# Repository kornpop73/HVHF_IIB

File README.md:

# HVHF_IIB
* Single-ended 65Vpp, 5ns amplifier with multiple output stages capable of driving capacitive loads up to 100pF. 
* This design is based on the circuit described in the 2005 paper by Holger Müller titled 'Fast High-Voltage Amplifiers for Driving Electro-Optic Modulators'.
* A link to the original paper can be found at the bottom of this page.
# High Voltage High Frequency IIB

## Repository Contents

* [**/Design Files**](https://github.com/kornpop73/HVHF_IIB/tree/01/Design%20Files) - Contains all ECAD and MCAD files for this board
* [**/Documentation**](https://github.com/kornpop73/HVHF_IIB/tree/01/Documentation) - Contains all documentation related to this product (schematics, data sheets, test results et.
* [**/Production**](https://github.com/kornpop73/HVHF_IIB/tree/01/Production) - Contains all production files for this product (gerbers, BOMs, etc.)
## Documentation
Copies of documentation are also saved in this repository

* **[Sources](https://github.com/kornpop73/HVHF_IIB/blob/01/Documentation/Schematic%20Diagrams/Müller_Paper.pdf)** - Holger Müller,'Fast High-Voltage Amplifiers for Driving Electro-Optic Modulators'
* **[Bill of Materials](https://github.com/kornpop73/HVHF_IIB/blob/01/Production/BOM)**

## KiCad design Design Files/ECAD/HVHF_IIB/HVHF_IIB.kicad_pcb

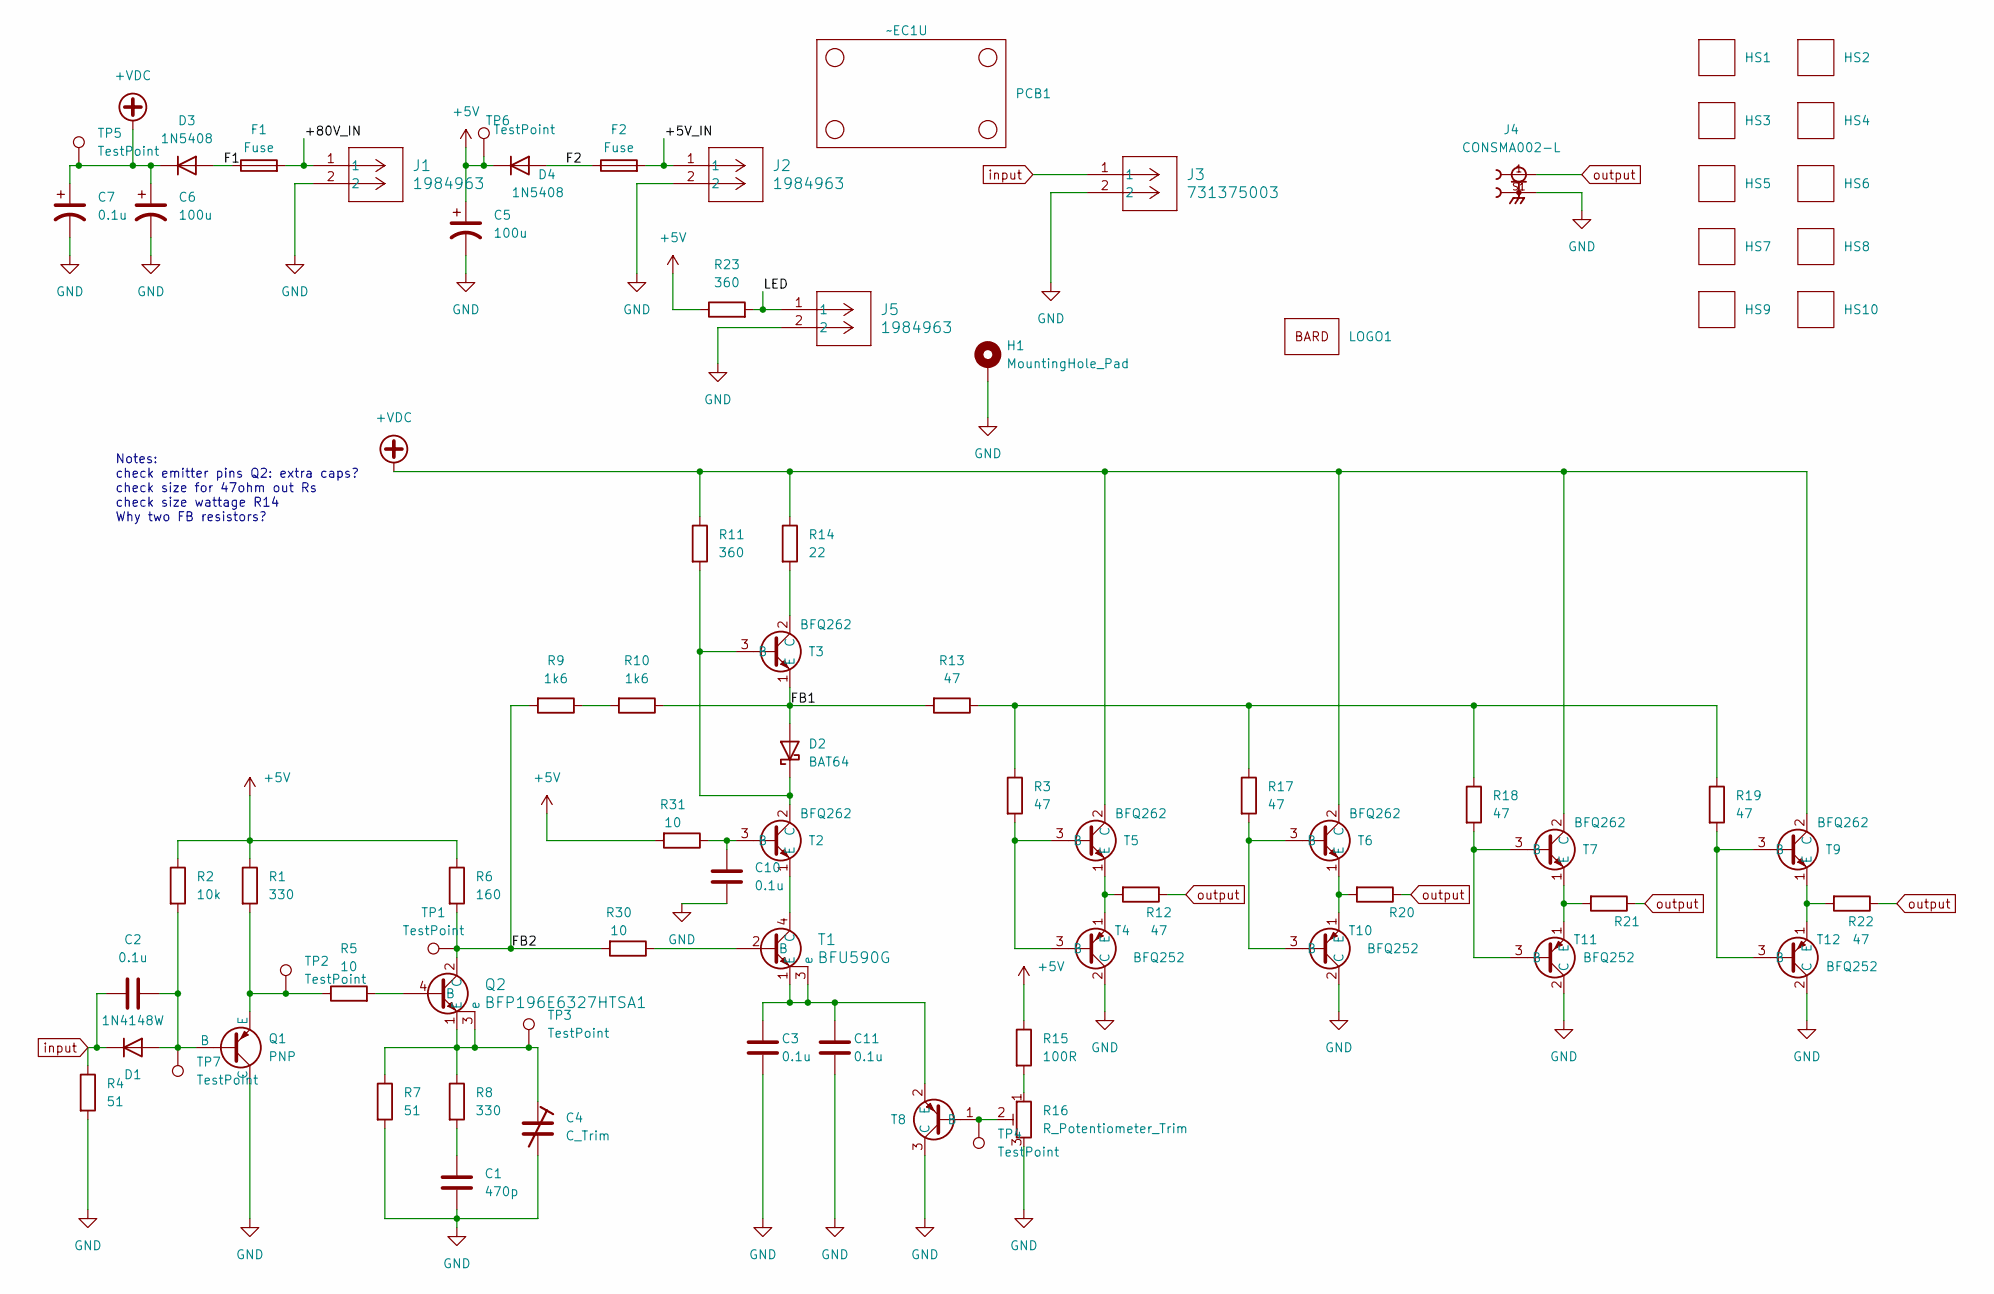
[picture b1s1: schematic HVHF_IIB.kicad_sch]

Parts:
C1: 470p; C_0805_2012Metric_Pad1.18x1.45mm_HandSolder
C2, C3, C10, C11: 0.1u; C_0805_2012Metric_Pad1.18x1.45mm_HandSolder
C4: C_Trim; PPZC80003
C5: 100u; C_1206_3216Metric_Pad1.33x1.80mm_HandSolder
C6: 100u; CAP_EEUED_125X25_PAN
C7: 0.1u; C_1206_3216Metric_Pad1.33x1.80mm_HandSolder
D1: 1N4148W; SOD123_MCC-M
D2: BAT64; SOT-23_ONS
D3, D4: 1N5408; D_DO-201AD_P15.24mm_Horizontal
F1, F2: Fuse; FUSE_4527
H1: MountingHole_Pad; Pin_D1.4mm_L8.5mm_W2.8mm_FlatFork
HS1, HS2, HS3, HS4, HS5, HS6, HS7, HS8, HS9, HS10: ATS_PCB1025
J1, J2, J5: 1984963; CONN_1984963
J3: 731375003; CONN_73137-5003_MOL
J4: CONSMA002-L; LINX_CONSMA002-L
LOGO1: LOGO_M
PCB1: ~EC1U; PCB_EC1U
Q1: PNP; SOT-23_ONS
Q2: BFP196E6327HTSA1; TRANS_BFP196E6327HTSA1_INF
R1, R8: 330; R_0805_2012Metric_Pad1.20x1.40mm_HandSolder
R2: 10k; R_0805_2012Metric_Pad1.20x1.40mm_HandSolder
R3, R13, R17, R18, R19: 47; R_0805_2012Metric_Pad1.20x1.40mm_HandSolder
R4, R7: 51; R_0805_2012Metric_Pad1.20x1.40mm_HandSolder
R5, R30, R31: 10; R_0805_2012Metric_Pad1.20x1.40mm_HandSolder
R6: 160; R_0805_2012Metric_Pad1.20x1.40mm_HandSolder
R9, R10: 1k6; RC2512N_VIS-M
R11: 360; PWWR0016
R12, R20, R21, R22: 47; RES_ALSR05_VIS
R14: 22; R_0805_2012Metric_Pad1.20x1.40mm_HandSolder
R15: 100R; R_0805_2012Metric_Pad1.20x1.40mm_HandSolder
R16: R_Potentiometer_Trim; POT_3296W
R23: 360; R_0805_2012Metric_Pad1.20x1.40mm_HandSolder
T1: BFU590G; SOT-223
T2, T3, T5, T6, T7, T9: BFQ262; TO126AV
T4, T10, T11, T12: BFQ252; TO126AV
T8: SOT23_NXP
TP1, TP2, TP3, TP4, TP5, TP6, TP7: TestPoint; TestPoint_Pad_D1.0mm

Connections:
+5V: C5.1, D4.1 (K), R1.1, R2.1, R6.1, R15.1, R23.1, R31.2, TP6.1
+VDC: C6.1, C7.1, D3.1 (K), R11.1, R14.1, T5.2 (C), T6.2 (C), T7.2 (C), T9.2 (C), TP5.1
/+5V_IN: F2.2, J2.1
/+80V_IN: F1.2, J1.1
/F1: D3.2 (A), F1.1
/F2: D4.2 (A), F2.1
/FB1: D2.1 (A), R10.1, R13.2, T3.1 (E)
/FB2: Q2.2 (C), R6.2, R9.2, R30.2, TP1.1
/LED: J5.1, R23.2
GND: C1.2, C3.2, C4.2, C5.2, C6.2, C7.2, C10.2, C11.2, H1.1, J1.2, J2.2, J3.2, J4.S1, J5.2, Q1.1 (C), R4.2, R7.2, R16.3, T4.2 (C), T8.3 (C), T10.2 (C), T11.2 (C), T12.2 (C)
unnamed: C1.1, R8.2
unnamed: C2.2, D1.2 (A), Q1.2 (B), R2.2, TP7.1
unnamed: D2.3 (K), R11.2, T2.2 (C), T3.3 (B)
unnamed: Q1.3 (E), R1.2, R5.1, TP2.1
unnamed: Q2.4 (B), R5.2
unnamed: C4.1, Q2.1 (E), Q2.3 (e), R7.1, R8.1, TP3.1
unnamed: R9.1, R10.2
unnamed: R3.1, R13.1, R17.1, R18.1, R19.1
unnamed: R15.2, R16.1
unnamed: R30.1, T1.2 (B)
unnamed: T1.4 (C), T2.1 (E)
unnamed: C3.1, C11.1, T1.1 (E), T1.3 (e), T8.2 (E)
unnamed: C10.1, R31.1, T2.3 (B)
unnamed: R14.2, T3.2 (C)
unnamed: R3.2, T4.3 (B), T5.3 (B)
unnamed: R12.2, T4.1 (E), T5.1 (E)
unnamed: R16.2, T8.1 (B), TP4.1
unnamed: R17.2, T6.3 (B), T10.3 (B)
unnamed: R20.2, T6.1 (E), T10.1 (E)
unnamed: R18.2, T7.3 (B), T11.3 (B)
unnamed: R21.2, T7.1 (E), T11.1 (E)
unnamed: R19.2, T9.3 (B), T12.3 (B)
unnamed: R22.2, T9.1 (E), T12.1 (E)
input: C2.1, D1.1 (K), J3.1, R4.1
output: J4.1, R12.1, R20.1, R21.1, R22.1

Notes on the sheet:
Notes: check emitter pins Q2: extra caps? check size for 47ohm out Rs check size wattage R14 Why two FB resistors?

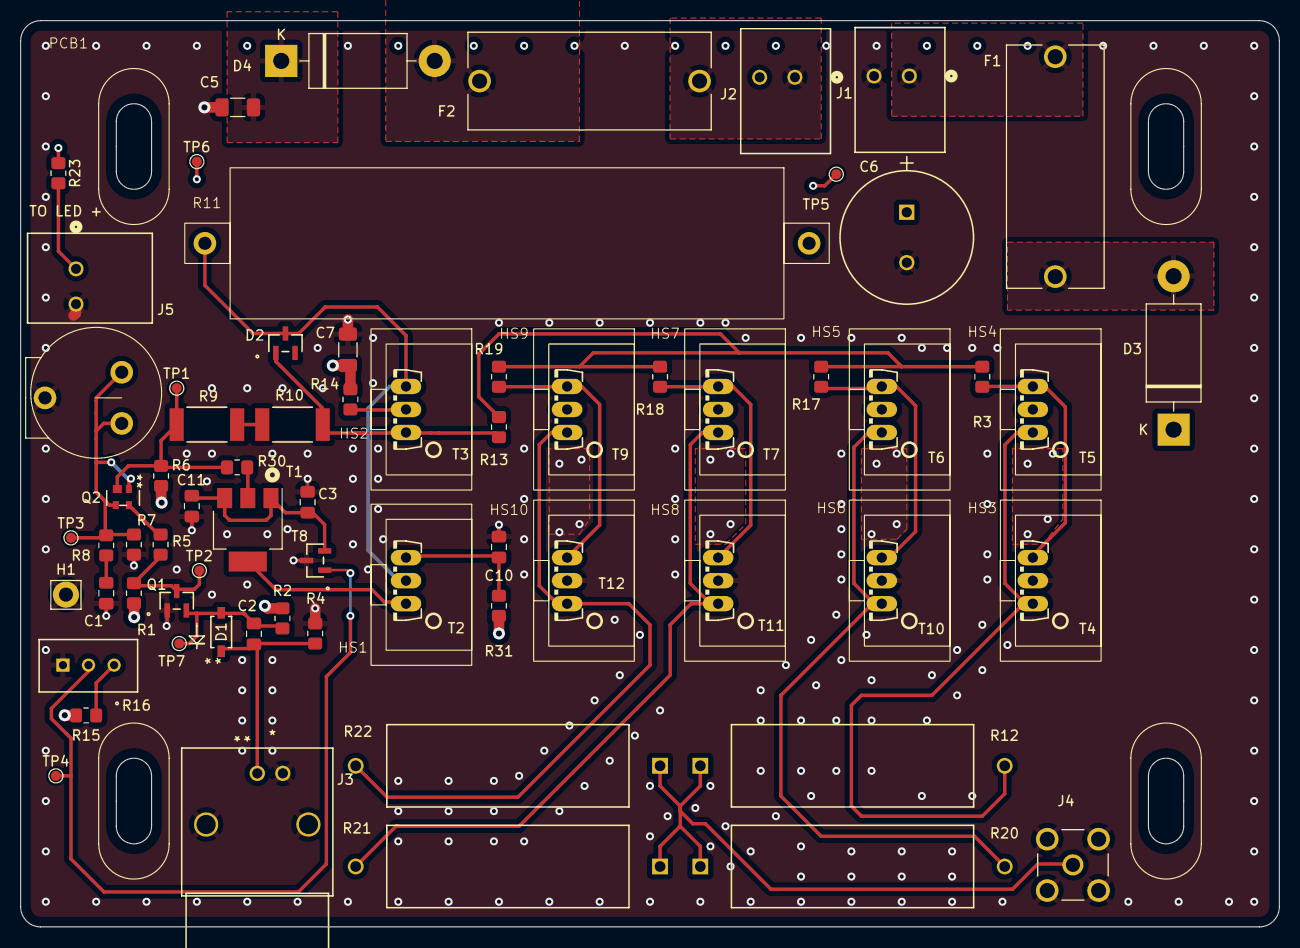
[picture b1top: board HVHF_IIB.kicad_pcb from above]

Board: 4 copper layers, 125.0 x 90.0 mm, 79 parts (1 on the bottom side), 35 nets.

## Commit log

2024-05-22 Initial commit basics
    adds spice files and eagle initials and data sheets
2024-05-22 adds cover image
2024-05-22 muller spell fix
2024-05-22 read me fix
2024-05-25 First KiCad submit
2024-05-28 schematic work
    adds components
    some foot prints
2024-05-29 adds footprints
2024-05-29 adds footprints
    3d models
2024-05-29 wrapped up schematic
    placed and routed all components on schematic
    adds all footprints
2024-05-31 PCB layout
    adds bard logo
    began pcb layout
    adds 3D model heat sink
2024-05-31 board layout
    sourced all components
    laid out all components
    designed all 3D models
2024-06-01 fixed Kicad error
    board already open error
    moved log files to Miscellaneous folder
2024-06-06 pcb work
    routing
    components
    3d models
    net classes
2024-06-06 began routing
2024-06-07 pcb routing
    routing
    updated pcb brd footprint
2024-06-07 routing
    Did DRC
    Did ERC (some errors to fix)
2024-06-07 small fix to pcb silk
2024-06-08 fixed orientation error T4,T10-T12
2024-06-08 fixed unconnected GND power pin
2024-06-08 fixes, adds, silk
    fixed Q1 rotation
    adds LED
    adds GND
2024-06-10 trace length matching
2024-06-10 Post DR
2024-06-14 stitching done
2024-06-14 checked footprints
2024-06-17 JLC SUBMIT 6/17/2024
2024-06-19 added build/production files submit 1-6/19
2024-06-19 BOM updates
2024-06-26 backups
